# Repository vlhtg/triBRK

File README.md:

# triBRK
<b>three Button Rhythm Keyboard</b> is a cheap and simple to produce input device for various rythm games, aiming to fill the niche of three button devices.

This is my first project both in KiCAD and in STM32Cube.

### Hardware

Built around a STM32 "blue-pill", it uses cheap commonly available parts and a 3D printed case. Unlike AVR-based alternatives this is even cheaper, as blue-pills are around 2-3 euros on Chinese websites. Initial designs had a STM32 chip and the auxilliary components placed directly on the board, but compared to just soldering a pre-made board this just resulted in useless complexity, longer building times and surprisingly, higher costs per unit.

### Images

<p float="left">
  
  &nbsp&nbsp&nbsp&nbsp&nbsp
  
</p>

### To be done

Even though the project is functional, there are still a lot of things that are left to be done:

* Implement an easy to use key programming method using the additional microswitches.
* Implement RGB LED functionality.
* Create variant with hot-swappable switch connectors.
* ~~Make 3D printed case.~~ DONE!

### How to make one

#### What you need

* A blue-pill STM32F103C6T6A board.
* A ST-Link (I have used a clone) and jumpers.
* A program to flash the board, for Linux I have used [this](https://github.com/stlink-org/stlink).
* Three mechanical switches of your choice, compatible with the MX switch layout, prefferably of the 5 pin variety.
* Two standard THT microswitches/buttons.
* A PCB ordered by using the provided Gerber files.

#### How to assemble

* Order the PCB from a custom manufacturer and wait for it to arrive (I have used JLCPCB, any alternative is just as good).
* If blue-pil does not come with soldered jumpers, solder the jumpers.
* Solder the two small microswitches and the three switches to the board.
* Solder the blue-pill on the board.
* Connect the blue-pill to your PC via the ST-Link.
* Flash it with the .bin available in Releases.
* Enjoy your new device!

### Thanks to:

* This library for the blue-pill footprint: https://github.com/Mr-JoE1/Kicad-STM32_bluebill
* This library for MX switches footprint: https://github.com/perigoso/keyswitch-kicad-library
* STM for the USB HID libraries that are included with STM32CubeIDE.
* [This](https://www.instructables.com/STM32-As-HID-USB-Keyboard-STM32-Tutorials/) guide for helping me navigate the Configuration interface of the IDE for the first time and explaining how to modify the generated code from the default mouse behaviour to a keyboard one.

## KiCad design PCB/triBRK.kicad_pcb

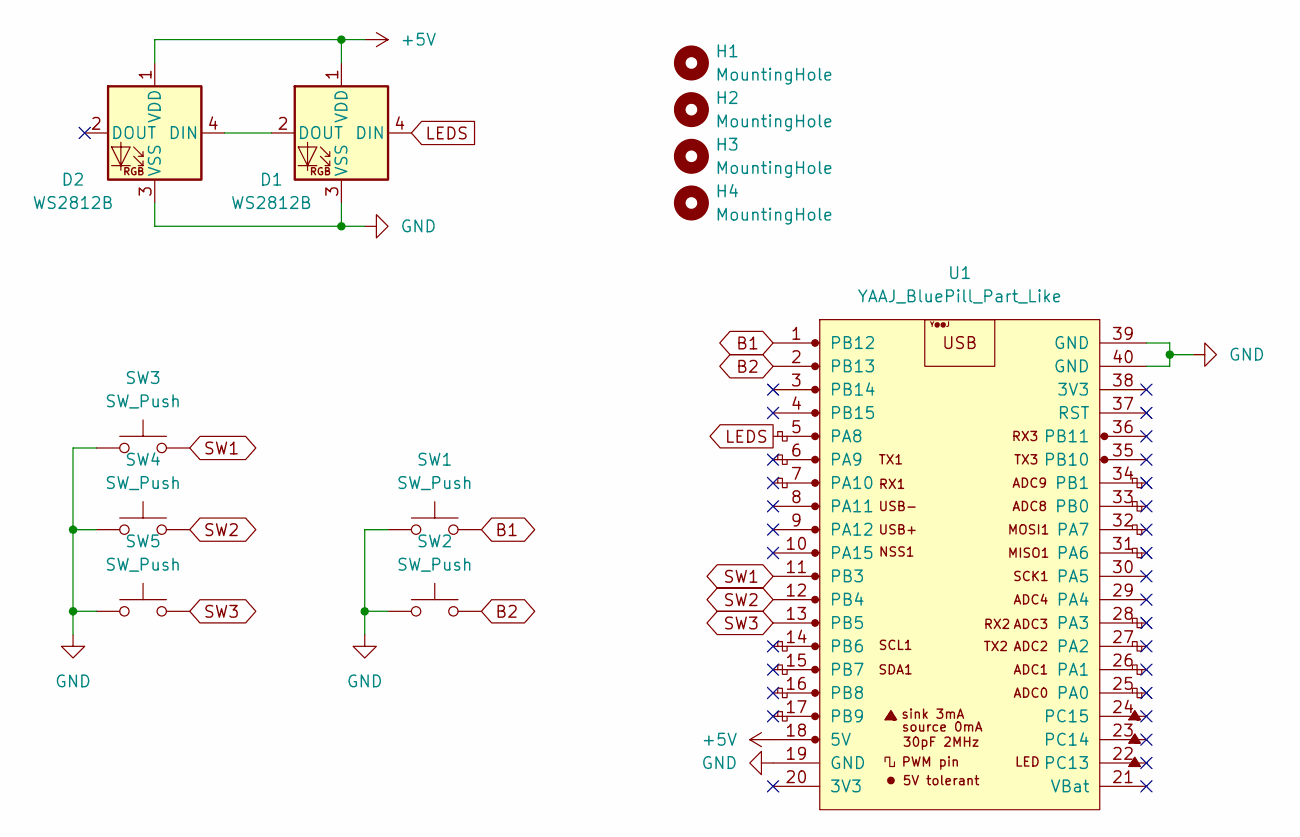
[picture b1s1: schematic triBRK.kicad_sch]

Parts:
D1, D2: WS2812B; LED_WS2812B_PLCC4_5.0x5.0mm_P3.2mm
H1, H2, H3, H4: MountingHole; MountingHole_2.2mm_M2_Pad_Via
SW1, SW2: SW_Push; SW_PUSH_6mm
SW3, SW4, SW5: SW_Push; SW_Cherry_MX_1.00u_PCB
U1: YAAJ_BluePill_Part_Like; YAAJ_BluePill_1

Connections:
+5V: D1.1 (VDD), D2.1 (VDD), U1.18 (5V)
B1: SW1.2, U1.1 (PB12)
B2: SW2.2, U1.2 (PB13)
GND: D1.3 (VSS), D2.3 (VSS), SW1.1, SW2.1, SW3.1, SW4.1, SW5.1, U1.19 (GND), U1.39 (GND), U1.40 (GND)
LEDS: D1.4 (DIN), U1.5 (PA8)
unnamed: D1.2 (DOUT), D2.4 (DIN)
SW1: SW3.2, U1.11 (PB3)
SW2: SW4.2, U1.12 (PB4)
SW3: SW5.2, U1.13 (PB5)

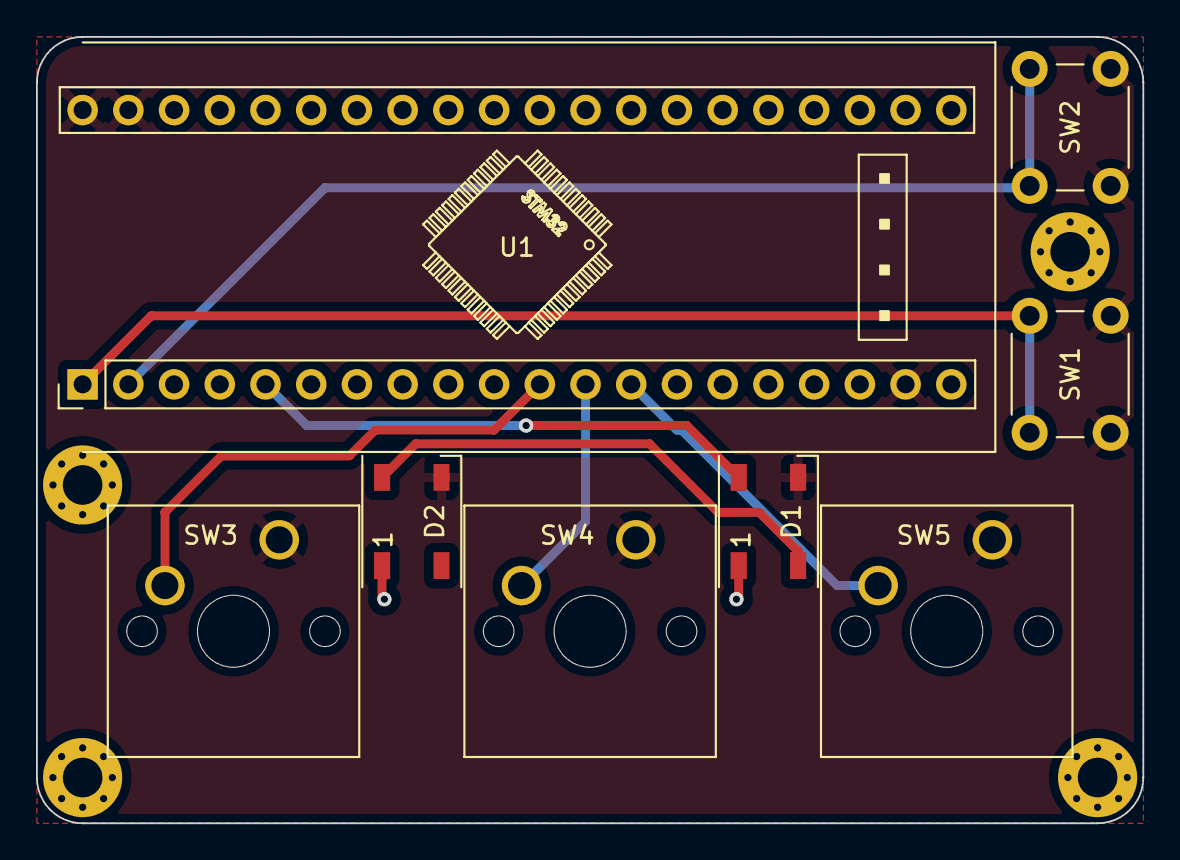
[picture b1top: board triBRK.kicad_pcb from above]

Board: 2 copper layers, 61.5 x 43.7 mm, 12 parts (0 on the bottom side), 9 nets.

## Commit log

2022-10-20 Uploaded PCB files
2022-10-20 Small changes
2022-10-20 Added .gitignore
2022-10-20 corrected typo
2022-10-20 Corrected .gitignore
2022-10-20 Added prl file
2022-10-20 Deleted prl file
2022-10-20 Rounder corners + other optimisations
2022-11-08 Changed holes specs and optimized wiring, nicer schematic also
2022-11-08 Modified silkscreen
2023-01-15 Added STM32 code
2023-01-15 Updated readme to reflect current state of project
2023-01-15 Added images of the first unit
2023-01-15 Corrected name
2023-01-15 Corrected typos
2023-03-26 Added 3D models for the case
2023-10-16 Updated readme with case info
